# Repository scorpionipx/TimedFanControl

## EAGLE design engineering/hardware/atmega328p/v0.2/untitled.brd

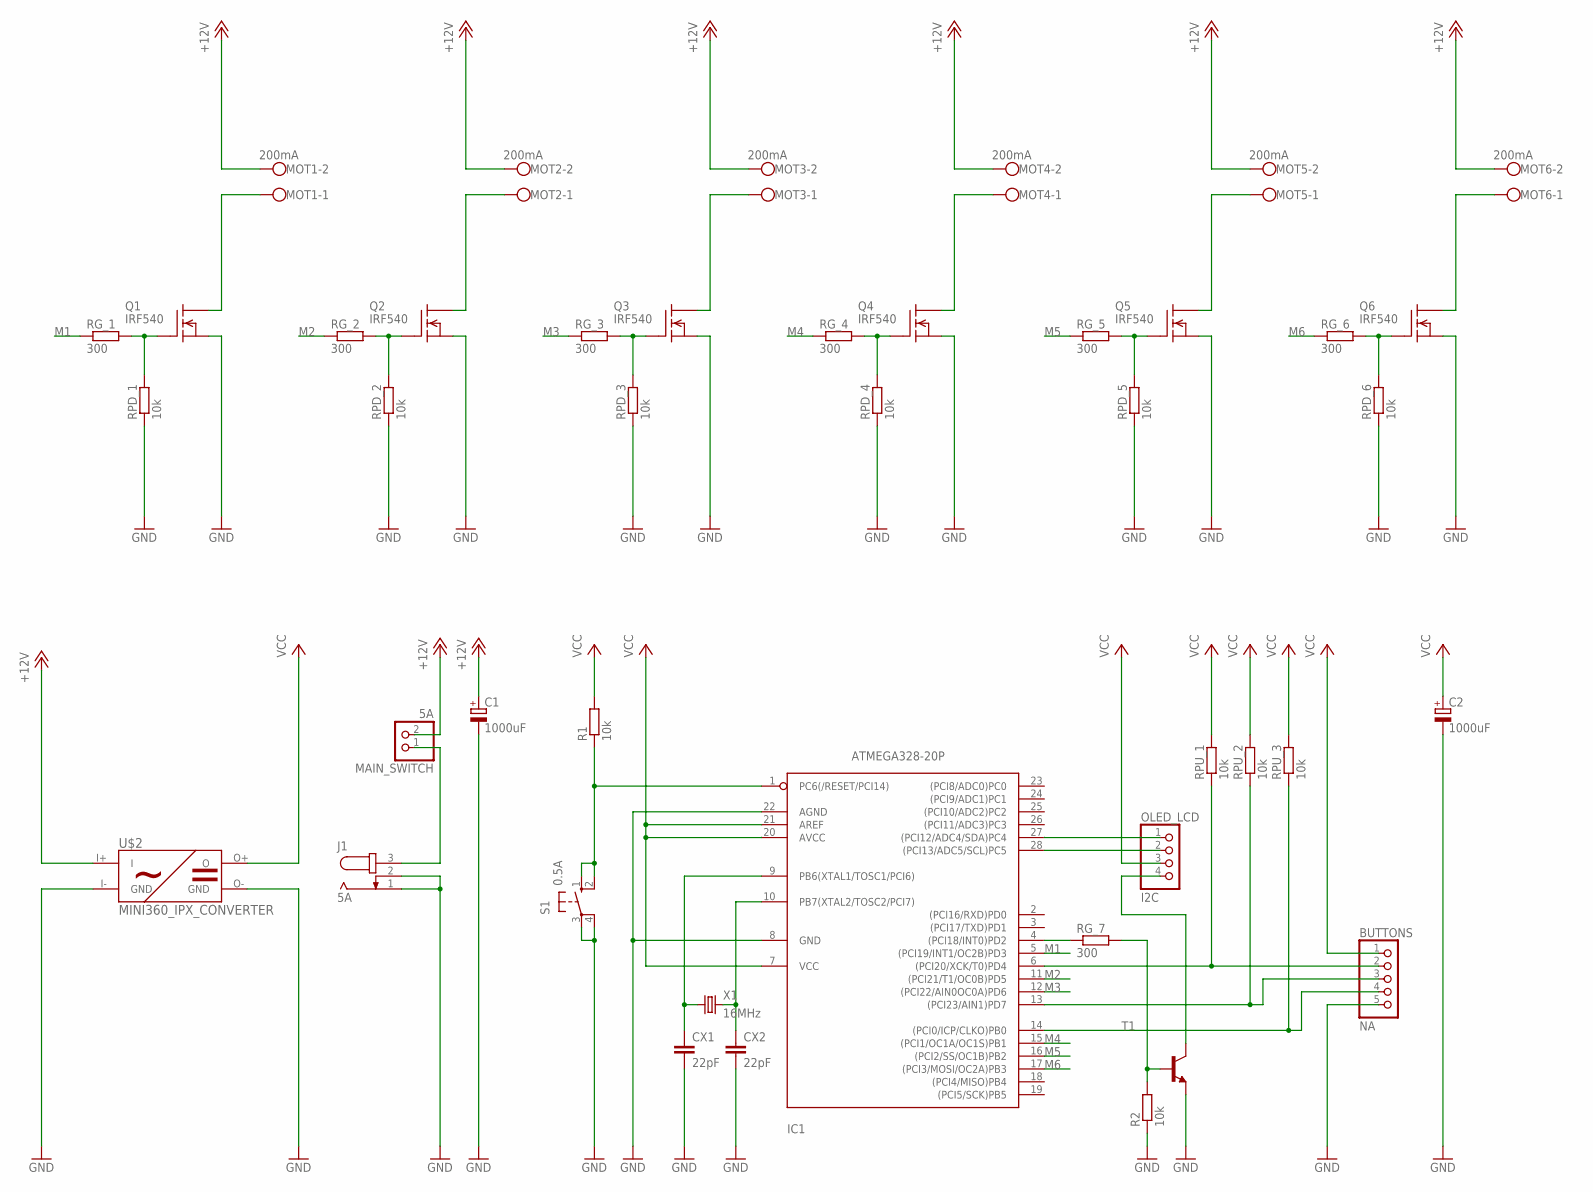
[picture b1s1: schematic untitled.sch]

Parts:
BUTTONS: NA; 1X05
C1, C2: 1000uF; E5-8,5
CX1, CX2: 22pF; C025-024X044
IC1: ATMEGA328-20P; DIL28-3
J1: 5A; SPC4078
MAIN_SWITCH: 5A; 1X02
MOT1, MOT2, MOT3, MOT4, MOT5, MOT6: 200mA; W237-102
OLED_LCD: I2C; 1X04
Q1, Q2, Q3, Q4, Q5, Q6: IRF540; TO220
R1, R2: 10k; 0207/10
RG_1, RG_2, RG_3, RG_4, RG_5, RG_6, RG_7: 300; 0207/10
RPD_1, RPD_2, RPD_3, RPD_4, RPD_5, RPD_6: 10k; 0207/10
RPU_1, RPU_2, RPU_3: 10k; 0207/10
S1: 0.5A; B3F-10XX
T1: 2N5551-NPN-TO92-CBE; TO92-CBE
U$2: MINI360_IPX_CONVERTER
X1: 16MHz; HC49/S

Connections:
+12V: C1.+, MAIN_SWITCH.2, MOT1.2, MOT2.2, MOT3.2, MOT4.2, MOT5.2, MOT6.2, U$2.I+ (I)
GND: BUTTONS.5, C1.-, C2.-, CX1.2, CX2.2, IC1.8 (GND), IC1.22 (AGND), J1.1, J1.2, Q1.3 (S), Q2.3 (S), Q3.3 (S), Q4.3 (S), Q5.3 (S), Q6.3 (S), R2.1, RPD_1.1, RPD_2.1, RPD_3.1, RPD_4.1, RPD_5.1, RPD_6.1, S1.3, S1.4 (P1), T1.E, U$2.I- (GND), U$2.O- (GND)
M1: IC1.5 ((PCI19/INT1/OC2B)PD3), RG_1.1
M2: IC1.11 ((PCI21/T1/OC0B)PD5), RG_2.1
M3: IC1.12 ((PCI22/AIN0OC0A)PD6), RG_3.1
M4: IC1.15 ((PCI1/OC1A/OC1S)PB1), RG_4.1
M5: IC1.16 ((PCI2/SS/OC1B)PB2), RG_5.1
M6: IC1.17 ((PCI3/MOSI/OC2A)PB3), RG_6.1
unnamed: IC1.1 (PC6(/RESET/PCI14)), R1.1, S1.1 (S), S1.2 (S1)
unnamed: CX1.1, IC1.9 (PB6(XTAL1/TOSC1/PCI6)), X1.1
unnamed: CX2.1, IC1.10 (PB7(XTAL2/TOSC2/PCI7)), X1.2
unnamed: Q1.1 (G), RG_1.2, RPD_1.2
unnamed: Q2.1 (G), RG_2.2, RPD_2.2
unnamed: MOT1.1, Q1.2 (D)
unnamed: MOT2.1, Q2.2 (D)
unnamed: Q3.1 (G), RG_3.2, RPD_3.2
unnamed: MOT3.1, Q3.2 (D)
unnamed: Q4.1 (G), RG_4.2, RPD_4.2
unnamed: MOT4.1, Q4.2 (D)
unnamed: Q5.1 (G), RG_5.2, RPD_5.2
unnamed: MOT5.1, Q5.2 (D)
unnamed: Q6.1 (G), RG_6.2, RPD_6.2
unnamed: MOT6.1, Q6.2 (D)
unnamed: IC1.27 ((PCI12/ADC4/SDA)PC4), OLED_LCD.1
unnamed: IC1.28 ((PCI13/ADC5/SCL)PC5), OLED_LCD.2
unnamed: BUTTONS.2, IC1.6 ((PCI20/XCK/T0)PD4), RPU_1.1
unnamed: BUTTONS.3, IC1.13 ((PCI23/AIN1)PD7), RPU_2.1
unnamed: BUTTONS.4, IC1.14 ((PCI0/ICP/CLKO)PB0), RPU_3.1
unnamed: J1.3, MAIN_SWITCH.1
unnamed: OLED_LCD.4, T1.C
unnamed: IC1.4 ((PCI18/INT0)PD2), RG_7.1
unnamed: R2.2, RG_7.2, T1.B
VCC: BUTTONS.1, C2.+, IC1.7 (VCC), IC1.20 (AVCC), IC1.21 (AREF), OLED_LCD.3, R1.2, RPU_1.2, RPU_2.2, RPU_3.2, U$2.O+ (O)

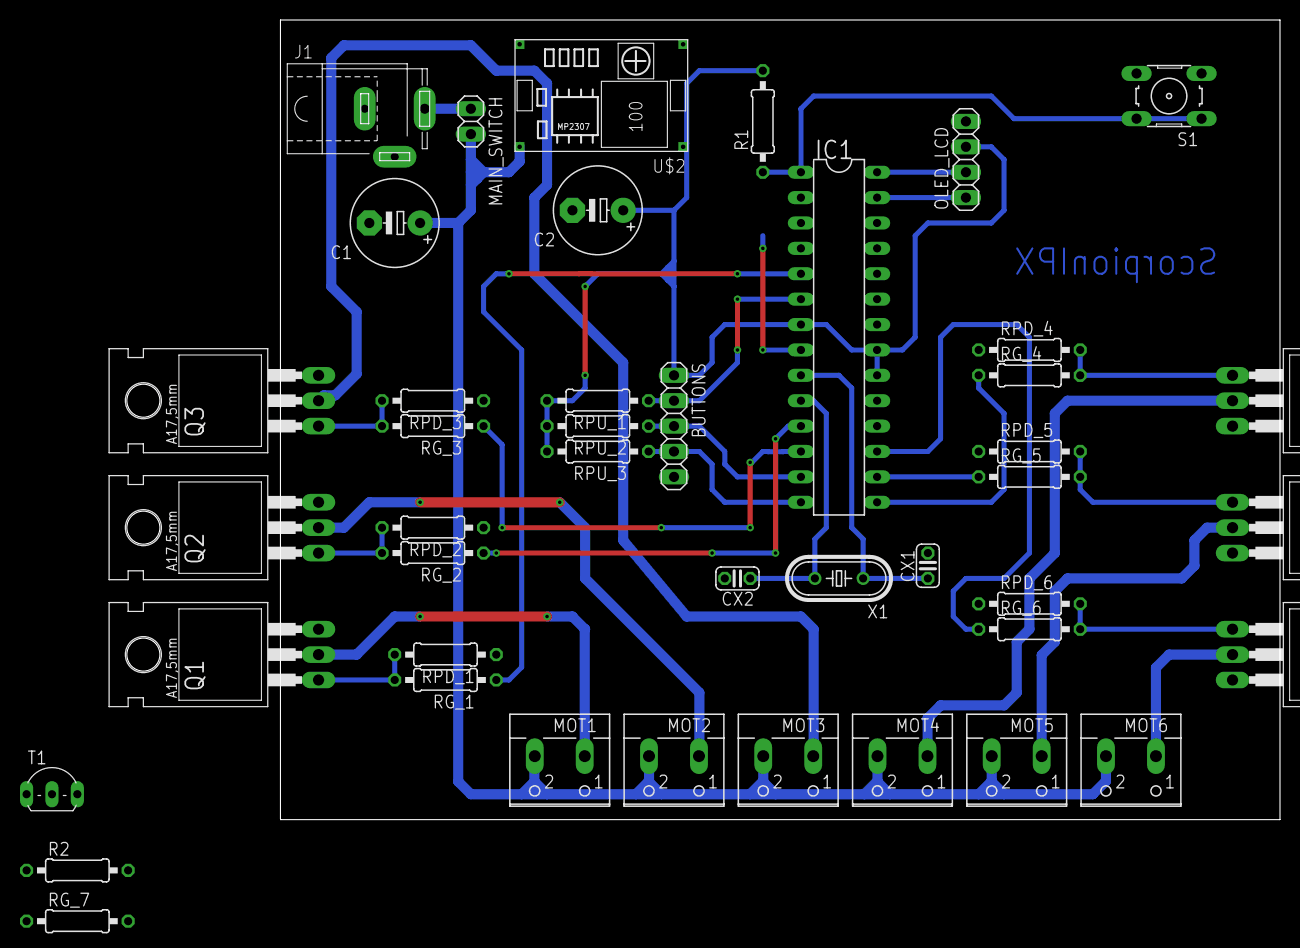
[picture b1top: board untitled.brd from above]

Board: 2 copper layers, 100.0 x 80.0 mm, 43 parts (0 on the bottom side), 33 nets.

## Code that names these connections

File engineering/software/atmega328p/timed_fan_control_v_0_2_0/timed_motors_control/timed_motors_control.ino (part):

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#define DEFAULT_T_OFF_HOURS 2 

// MOTORS HARDWARE SETTINGS
#define MOTOR_1_PIN  3  // digital pin used to command driver for motor 1 (PD3)
#define MOTOR_2_PIN  5  // digital pin used to command driver for motor 2 (PD5)
#define MOTOR_3_PIN  6  // digital pin used to command driver for motor 3 (PD6)
#define MOTOR_4_PIN  9  // digital pin used to command driver for motor 4 (PB1)
#define MOTOR_5_PIN 10  // digital pin used to command driver for motor 5 (PB2)
#define MOTOR_6_PIN 11  // digital pin used to command driver for motor 6 (PB3)

// BUTTONS HARDWARE SETTINGS
#define BUTTON_1_PIN 4  // digital pin used to read button state (PD4) - used to change selected config value
#define BUTTON_2_PIN 7  // digital pin used to read button state (PD7) - used to select next config value
#define BUTTON_3_PIN 8  // digital pin used to read button state (PB0) - used to reset internal timer

// DISPLAY HARDWARE SETTINGS
#define DISPLAY_SWITCH_PIN 2  // digital pin used to control display's power switch (PD2)

// GENERIC
#define TRUE 1
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
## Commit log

2018-06-27 Arduino required libs
2018-06-27 useful links
2018-06-27 uC datasheet
2018-06-27 software sketch
2018-06-29 uC pinout and buttons update
2018-07-02 Stable version
2018-08-21 new SW version
2018-08-22 updated descriptions
2018-08-22 updated comments and default imes values
2018-08-22 initial schematic
2018-08-22 layout ready to print
2018-08-25 comment pn ussage for display power switching
2018-08-25 Added display switch (TO SCHEMATIC ONLY!!!!!!!!!)
2018-08-25 final product image
